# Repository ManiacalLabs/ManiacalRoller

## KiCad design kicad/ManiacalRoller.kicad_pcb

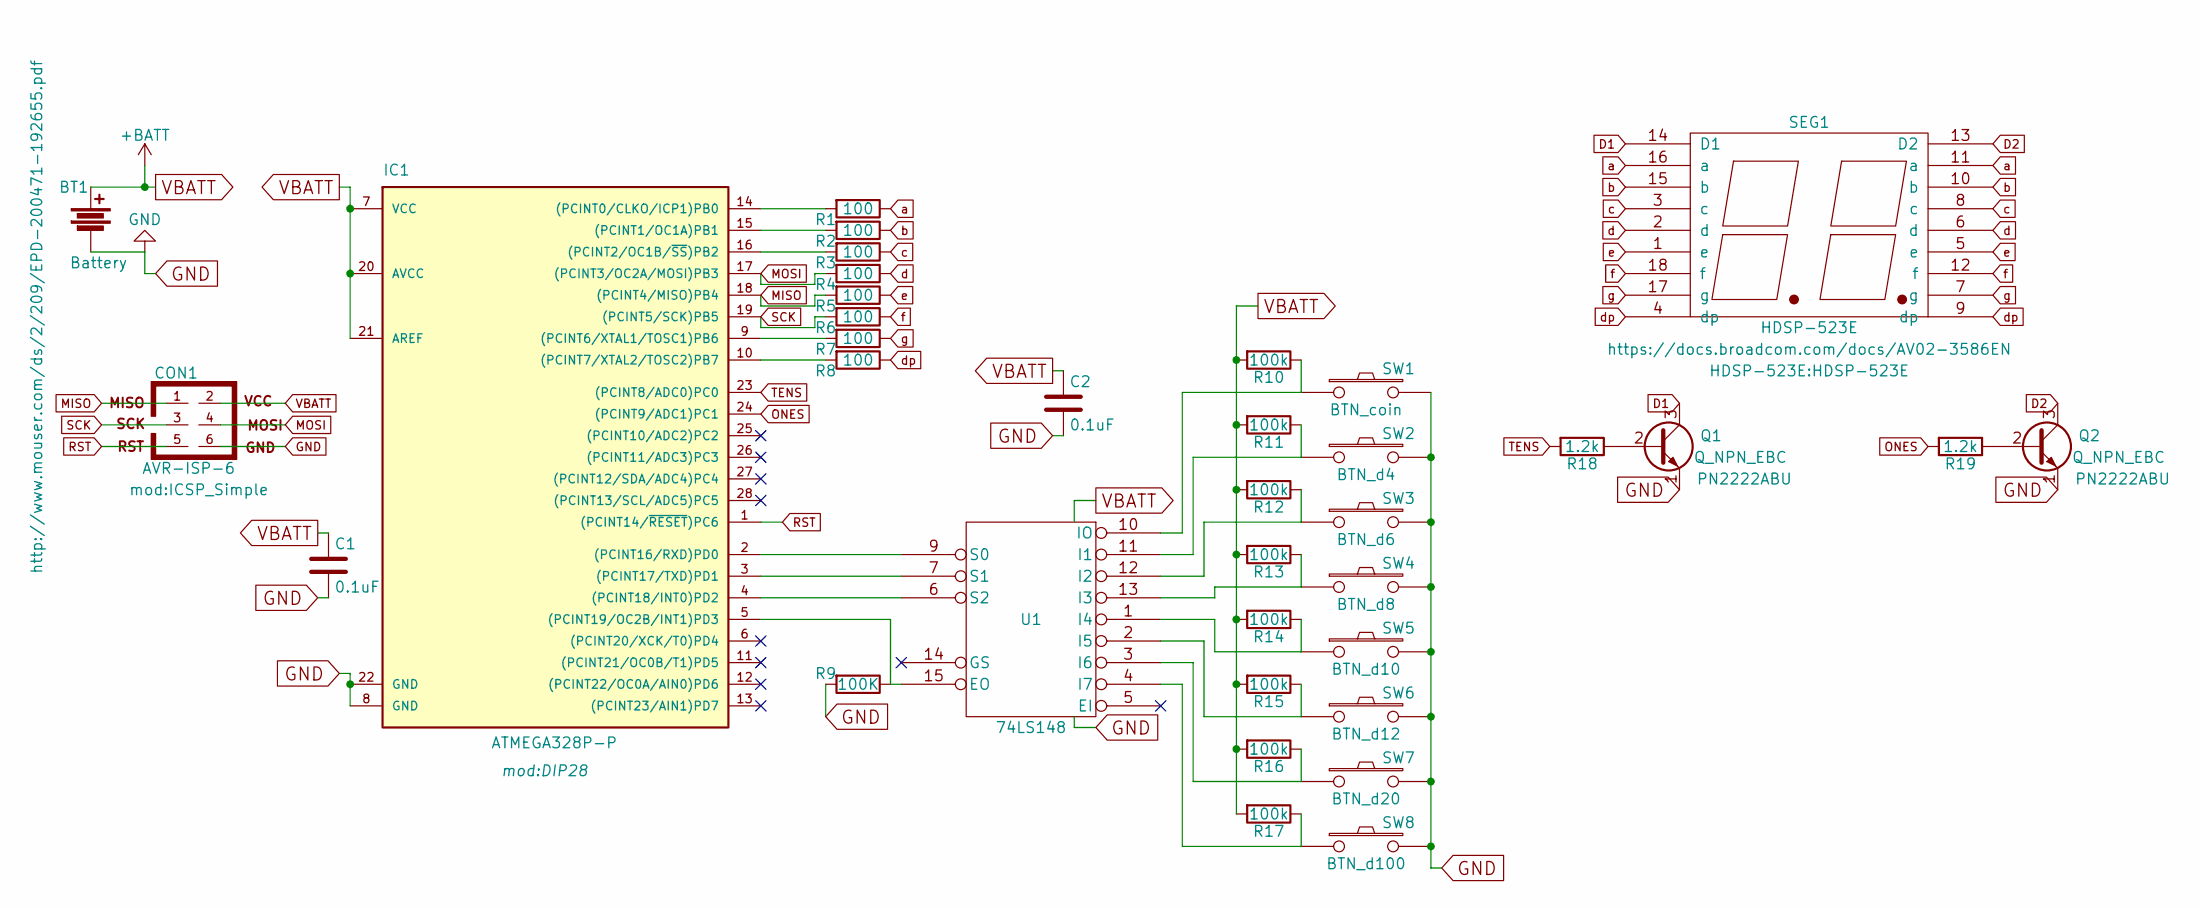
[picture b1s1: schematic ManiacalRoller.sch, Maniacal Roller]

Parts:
BT1: Battery; 2xAABatteryHolder_24mm5x53mm
C1, C2: 0.1uF; C_Disc_D3.0mm_W1.6mm_P2.50mm
CON1: AVR-ISP-6; ICSP_Simple
IC1: ATMEGA328P-P; DIP28
Q1, Q2: Q_NPN_EBC; TO-92_Inline_Narrow_Oval
R1, R2, R3, R4, R5, R6, R7, R8: 100; R_Axial_DIN0204_L3.6mm_D1.6mm_P5.08mm_Horizontal
R9: 100K; R_Axial_DIN0204_L3.6mm_D1.6mm_P5.08mm_Horizontal
R10, R11, R12, R13, R14, R15, R16, R17: 100k; R_Axial_DIN0204_L3.6mm_D1.6mm_P5.08mm_Horizontal
R18, R19: 1.2k; R_Axial_DIN0204_L3.6mm_D1.6mm_P5.08mm_Horizontal
SEG1: HDSP-523E
SW1: BTN_coin; SW_PUSH_6mm
SW2: BTN_d4; SW_PUSH_6mm
SW3: BTN_d6; SW_PUSH_6mm
SW4: BTN_d8; SW_PUSH_6mm
SW5: BTN_d10; SW_PUSH_6mm
SW6: BTN_d12; SW_PUSH_6mm
SW7: BTN_d20; SW_PUSH_6mm
SW8: BTN_d100; SW_PUSH_6mm
U1: 74LS148; DIP-16_W7.62mm_Socket_LongPads

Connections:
D1: Q1.3 (C), SEG1.14 (D1)
D2: Q2.3 (C), SEG1.13 (D2)
GND: BT1.2, C1.2, C2.2, CON1.6, IC1.8 (GND), IC1.22 (GND), Q1.1 (E), Q2.1 (E), R9.2, SW1.2, SW2.2, SW3.2, SW4.2, SW5.2, SW6.2, SW7.2, SW8.2, U1.8 (GND)
MISO: CON1.1, IC1.18 ((PCINT4/MISO)PB4), R5.2
MOSI: CON1.4, IC1.17 ((PCINT3/OC2A/MOSI)PB3), R4.2
unnamed: IC1.2 ((PCINT16/RXD)PD0), U1.9 (S0)
unnamed: IC1.3 ((PCINT17/TXD)PD1), U1.7 (S1)
unnamed: IC1.4 ((PCINT18/INT0)PD2), U1.6 (S2)
unnamed: IC1.5 ((PCINT19/OC2B/INT1)PD3), R9.1, U1.15 (EO)
unnamed: IC1.9 ((PCINT6/XTAL1/TOSC1)PB6), R7.2
unnamed: IC1.10 ((PCINT7/XTAL2/TOSC2)PB7), R8.2
unnamed: IC1.14 ((PCINT0/CLKO/ICP1)PB0), R1.2
unnamed: IC1.15 ((PCINT1/OC1A)PB1), R2.2
unnamed: IC1.16 ((PCINT2/OC1B/~SS~)PB2), R3.2
unnamed: Q1.2 (B), R18.1
unnamed: Q2.2 (B), R19.1
unnamed: R10.1, SW1.1, U1.10 (IO)
unnamed: R11.1, SW2.1, U1.11 (I1)
unnamed: R12.1, SW3.1, U1.12 (I2)
unnamed: R13.1, SW4.1, U1.13 (I3)
unnamed: R14.1, SW5.1, U1.1 (I4)
unnamed: R15.1, SW6.1, U1.2 (I5)
unnamed: R16.1, SW7.1, U1.3 (I6)
unnamed: R17.1, SW8.1, U1.4 (I7)
ONES: IC1.24 ((PCINT9/ADC1)PC1), R19.2
RST: CON1.5, IC1.1 ((PCINT14/~RESET~)PC6)
SCK: CON1.3, IC1.19 ((PCINT5/SCK)PB5), R6.2
TENS: IC1.23 ((PCINT8/ADC0)PC0), R18.2
VBATT: BT1.1, C1.1, C2.1, CON1.2, IC1.7 (VCC), IC1.20 (AVCC), IC1.21 (AREF), R10.2, R11.2, R12.2, R13.2, R14.2, R15.2, R16.2, R17.2, U1.16 (VCC)
a: R1.1, SEG1.11 (a), SEG1.16 (a)
b: R2.1, SEG1.10 (b), SEG1.15 (b)
c: R3.1, SEG1.3 (c), SEG1.8 (c)
d: R4.1, SEG1.2 (d), SEG1.6 (d)
dp: R8.1, SEG1.4 (dp), SEG1.9 (dp)
e: R5.1, SEG1.1 (e), SEG1.5 (e)
f: R6.1, SEG1.12 (f), SEG1.18 (f)
g: R7.1, SEG1.7 (g), SEG1.17 (g)

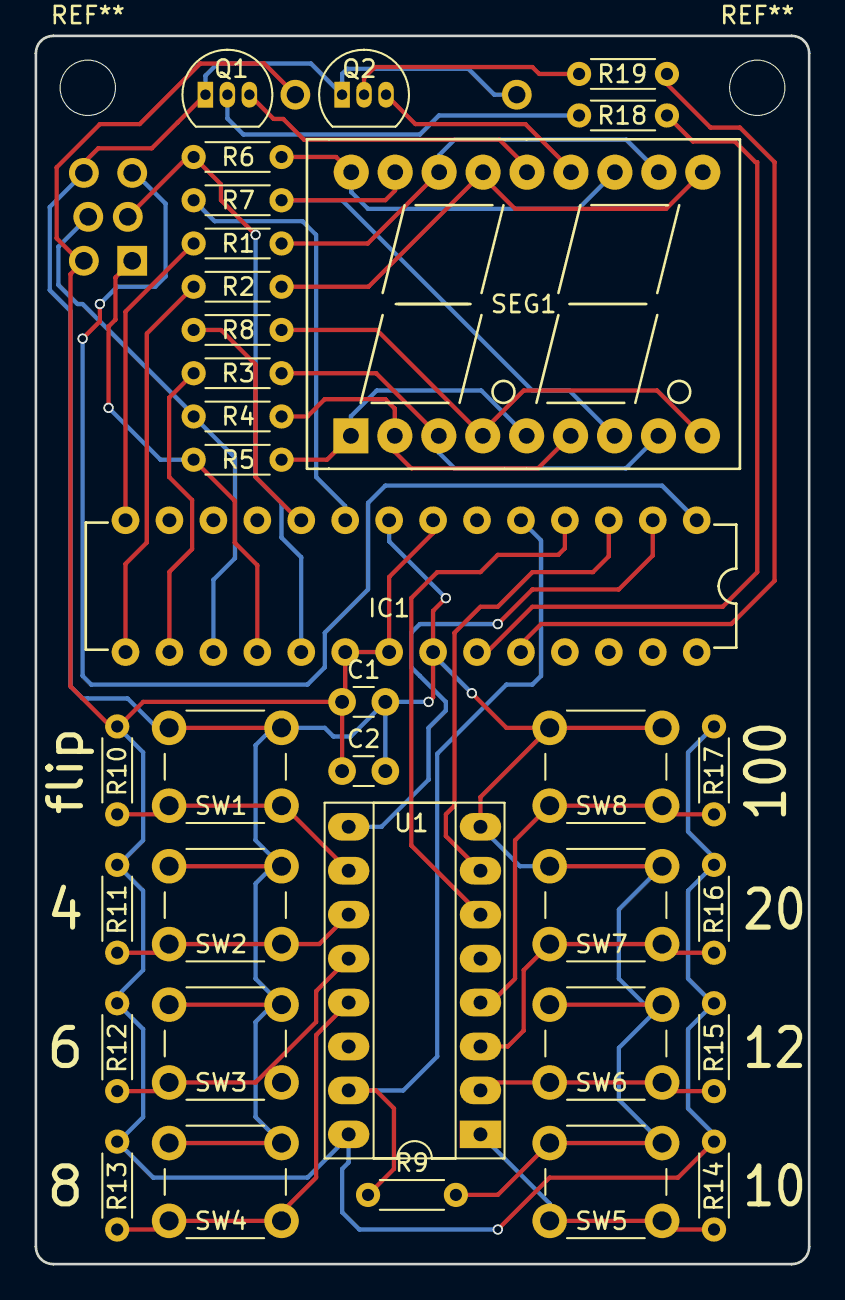
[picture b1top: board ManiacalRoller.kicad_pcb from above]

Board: 2 copper layers, 44.7 x 71.0 mm, 36 parts (1 on the bottom side), 37 nets.

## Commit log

2017-02-08 Update LICENSE
2017-02-08 Added kicad folder and CERN license
2017-02-08 Created KiCAD project, added footprints
2017-02-08 Created HDSP-523E Footprint
2017-02-08 Created HDSP-523E Schematic symbol
2017-02-11 Added more components
2017-02-27 Added to schematic
2017-03-04 PCB Layout
2017-03-05 Redid layout, laid tracks
2017-03-05 changed coin to flip, adjusted dice labels
2017-03-05 Tweaked logo size/position
2017-03-20 Bat Hlder on back
2017-03-20 Added test file with PCB sizing notes
